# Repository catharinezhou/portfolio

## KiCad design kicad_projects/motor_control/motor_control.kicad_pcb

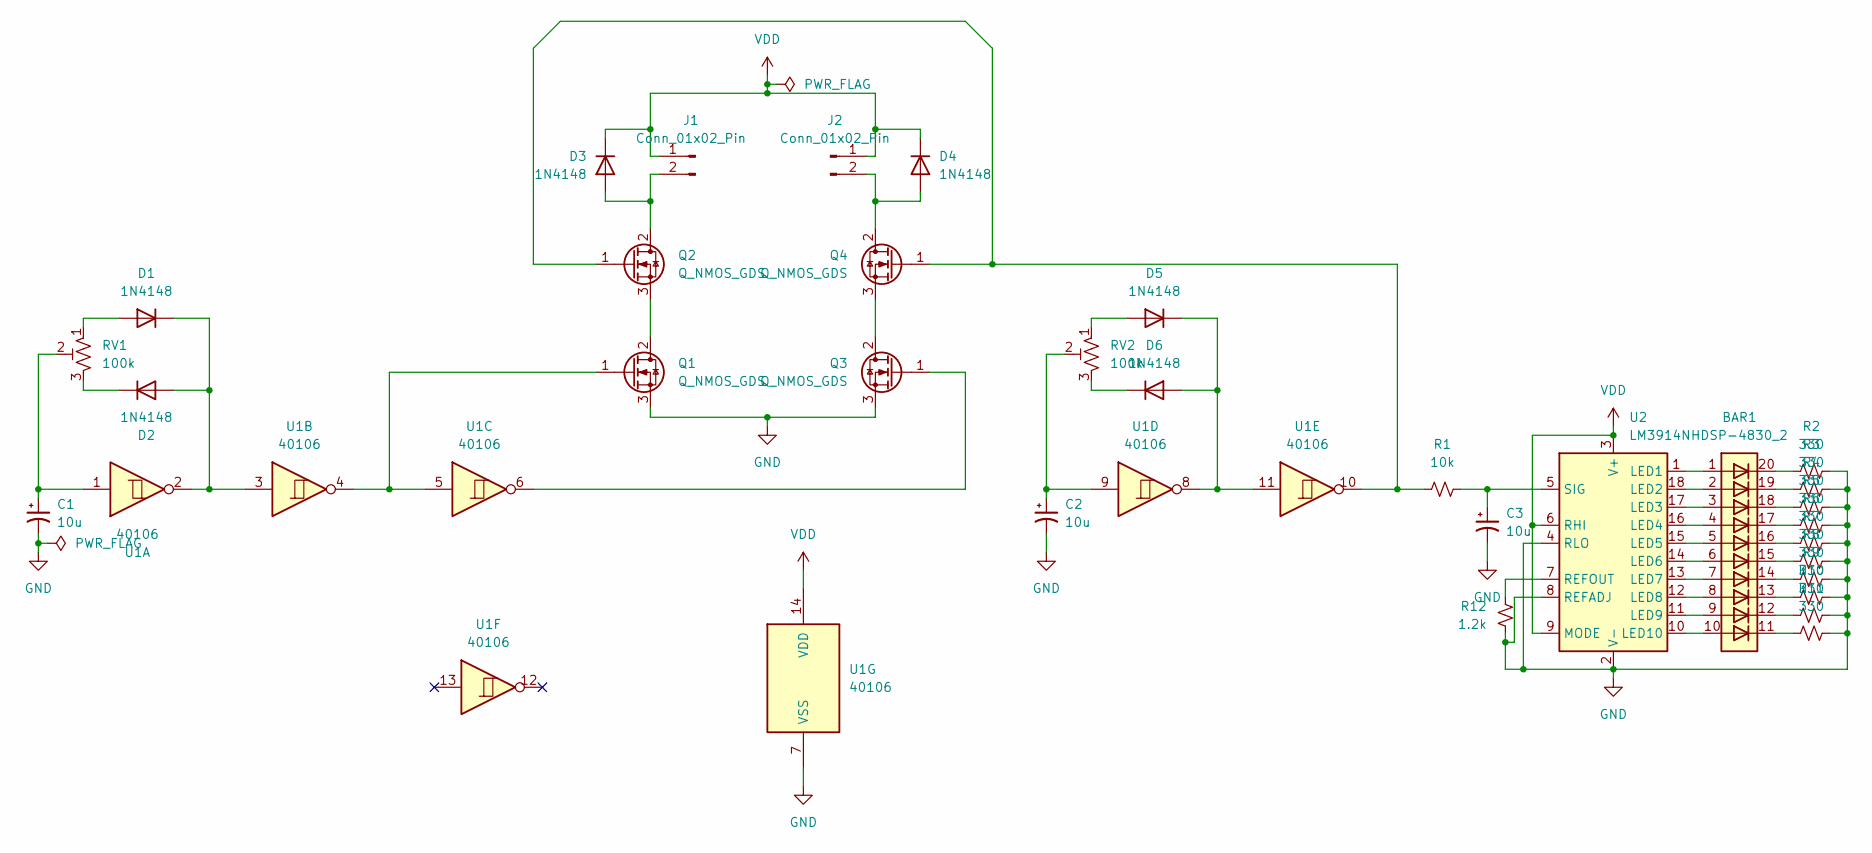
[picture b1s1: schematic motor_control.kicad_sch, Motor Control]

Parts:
BAR1: HDSP-4830_2; HDSP-4830
C1, C2, C3: 10u; CP_Radial_D6.3mm_P2.50mm
D1, D2, D3, D4, D5, D6: 1N4148; D_DO-35_SOD27_P7.62mm_Horizontal
J1, J2: Conn_01x02_Pin; TerminalBlock_Phoenix_MKDS-1,5-2-5.08_1x02_P5.08mm_Horizont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
Q1, Q2, Q3, Q4: Q_NMOS_GDS; TO-220-3_Vertical
R1: 10k; R_Axial_DIN0207_L6.3mm_D2.5mm_P10.16mm_Horizontal
R2, R3, R4, R5, R6, R7, R8, R9, R10, R11: 330; R_Axial_DIN0207_L6.3mm_D2.5mm_P10.16mm_Horizontal
R12: 1.2k; R_Axial_DIN0207_L6.3mm_D2.5mm_P10.16mm_Horizontal
RV1, RV2: 100k; Potentiometer_Bourns_3386P_Vertical
U1: 40106; DIP-14_W7.62mm
U2: LM3914N; DIP-18_W7.62mm

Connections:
GND: C1.2, C2.2, C3.2, Q1.3 (S), Q3.3 (S), R2.2, R3.2, R4.2, R5.2, R6.2, R7.2, R8.2, R9.2, R10.2, R11.2, R12.2, U1.7 (VSS), U2.2 (V-), U2.4 (RLO), U2.8 (REFADJ)
unnamed: BAR1.11 (K), R11.1
unnamed: BAR1.12 (K), R10.1
unnamed: BAR1.13 (K), R9.1
unnamed: BAR1.14 (K), R8.1
unnamed: BAR1.15 (K), R7.1
unnamed: BAR1.16 (K), R6.1
unnamed: BAR1.17 (K), R5.1
unnamed: BAR1.18 (K), R4.1
unnamed: BAR1.19 (K), R3.1
unnamed: BAR1.20 (K), R2.1
unnamed: C1.1, RV1.2, U1.1
unnamed: C2.1, RV2.2, U1.9
unnamed: D1.2 (A), RV1.1
unnamed: D1.1 (K), D2.2 (A), U1.2, U1.3
unnamed: D2.1 (K), RV1.3
unnamed: D3.2 (A), J1.2, Q2.2 (D)
unnamed: D4.2 (A), J2.2, Q4.2 (D)
unnamed: D5.2 (A), RV2.1
unnamed: D5.1 (K), D6.2 (A), U1.8, U1.11
unnamed: D6.1 (K), RV2.3
unnamed: Q1.2 (D), Q2.3 (S)
unnamed: Q1.1 (G), U1.4, U1.5
unnamed: Q2.1 (G), Q4.1 (G), R1.1, U1.10
unnamed: Q3.2 (D), Q4.3 (S)
unnamed: Q3.1 (G), U1.6
unnamed: BAR1.1 (A), U2.1 (LED1)
unnamed: BAR1.2 (A), U2.18 (LED2)
unnamed: BAR1.3 (A), U2.17 (LED3)
unnamed: BAR1.4 (A), U2.16 (LED4)
unnamed: BAR1.5 (A), U2.15 (LED5)
unnamed: BAR1.6 (A), U2.14 (LED6)
unnamed: BAR1.7 (A), U2.13 (LED7)
unnamed: BAR1.8 (A), U2.12 (LED8)
unnamed: BAR1.9 (A), U2.11 (LED9)
unnamed: BAR1.10 (A), U2.10 (LED10)
unnamed: R12.1, U2.7 (REFOUT)
unnamed: C3.1, R1.2, U2.5 (SIG)
VDD: D3.1 (K), D4.1 (K), J1.1, J2.1, U1.14 (VDD), U2.3 (V+), U2.6 (RHI), U2.9 (MODE)

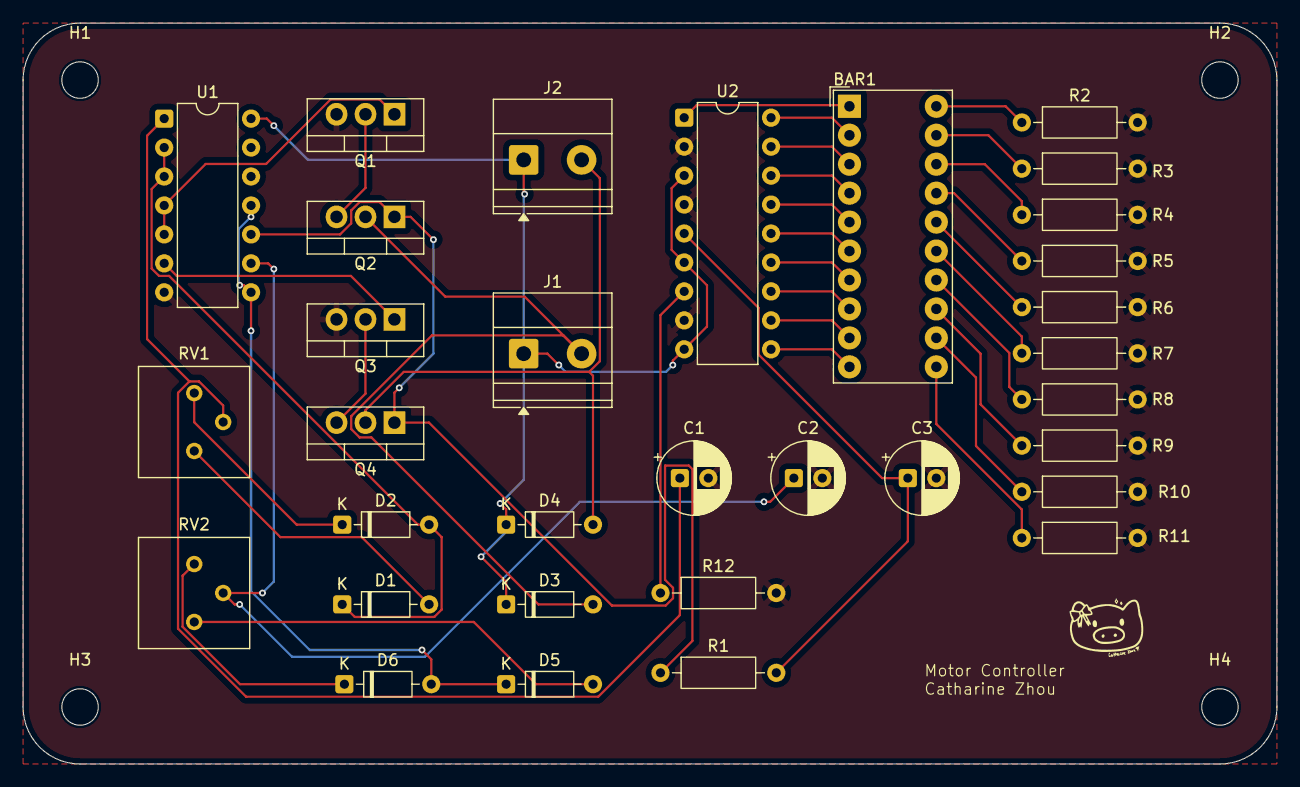
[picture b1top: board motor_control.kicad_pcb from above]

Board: 2 copper layers, 110.0 x 65.0 mm, 36 parts (0 on the bottom side), 39 nets.

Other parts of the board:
H1, H2, H3, H4: MountingHole; MountingHole_3.2mm_M3

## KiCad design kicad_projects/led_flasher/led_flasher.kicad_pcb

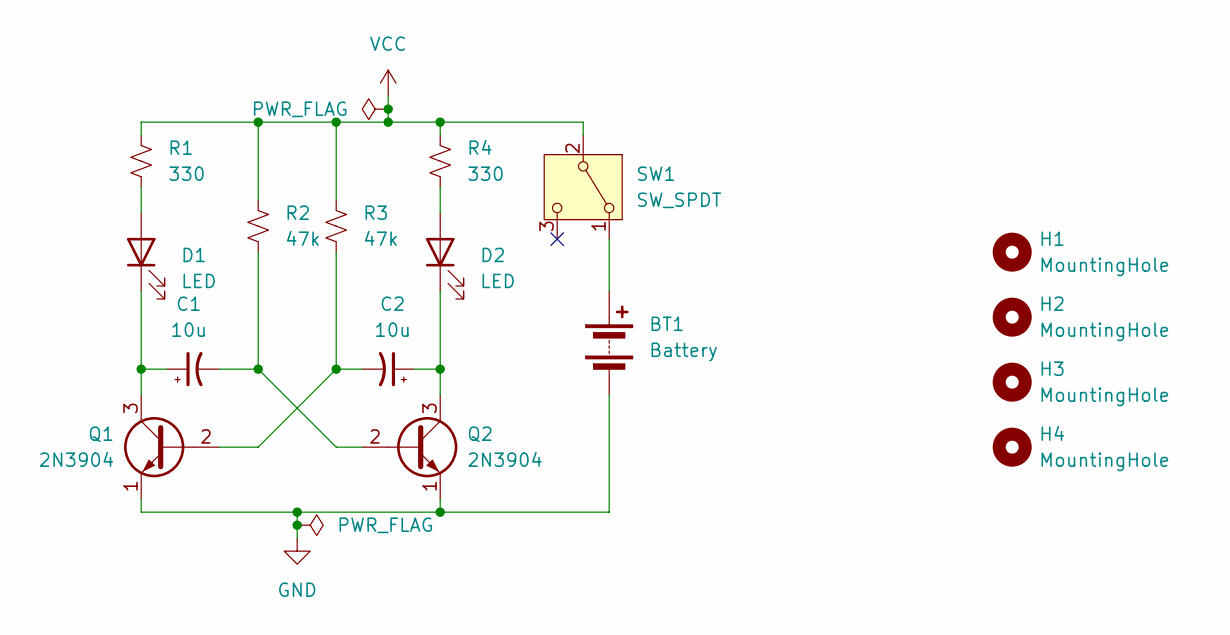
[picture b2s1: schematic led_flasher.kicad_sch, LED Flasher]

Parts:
BT1: Battery; BatteryHolder_Keystone_2479_3xAAA
C1, C2: 10u; CP_Radial_D6.3mm_P2.50mm
D1, D2: LED; LED_D5.0mm
H1, H2, H3, H4: MountingHole; MountingHole_3.2mm_M3
Q1, Q2: 2N3904; TO-92_Inline
R1, R4: 330; R_Axial_DIN0207_L6.3mm_D2.5mm_P10.16mm_Horizontal
R2, R3: 47k; R_Axial_DIN0207_L6.3mm_D2.5mm_P10.16mm_Horizontal
SW1: SW_SPDT; SW_E-Switch_EG1224_SPDT_Angled

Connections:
GND: BT1.2 (-), Q1.1 (E), Q2.1 (E)
unnamed: BT1.1 (+), SW1.1 (A)
unnamed: D1.2 (A), R1.2
unnamed: C1.1, D1.1 (K), Q1.3 (C)
unnamed: D2.2 (A), R4.2
unnamed: C2.1, D2.1 (K), Q2.3 (C)
unnamed: C2.2, Q1.2 (B), R3.2
unnamed: C1.2, Q2.2 (B), R2.2
VCC: R1.1, R2.1, R3.1, R4.1, SW1.2 (B)

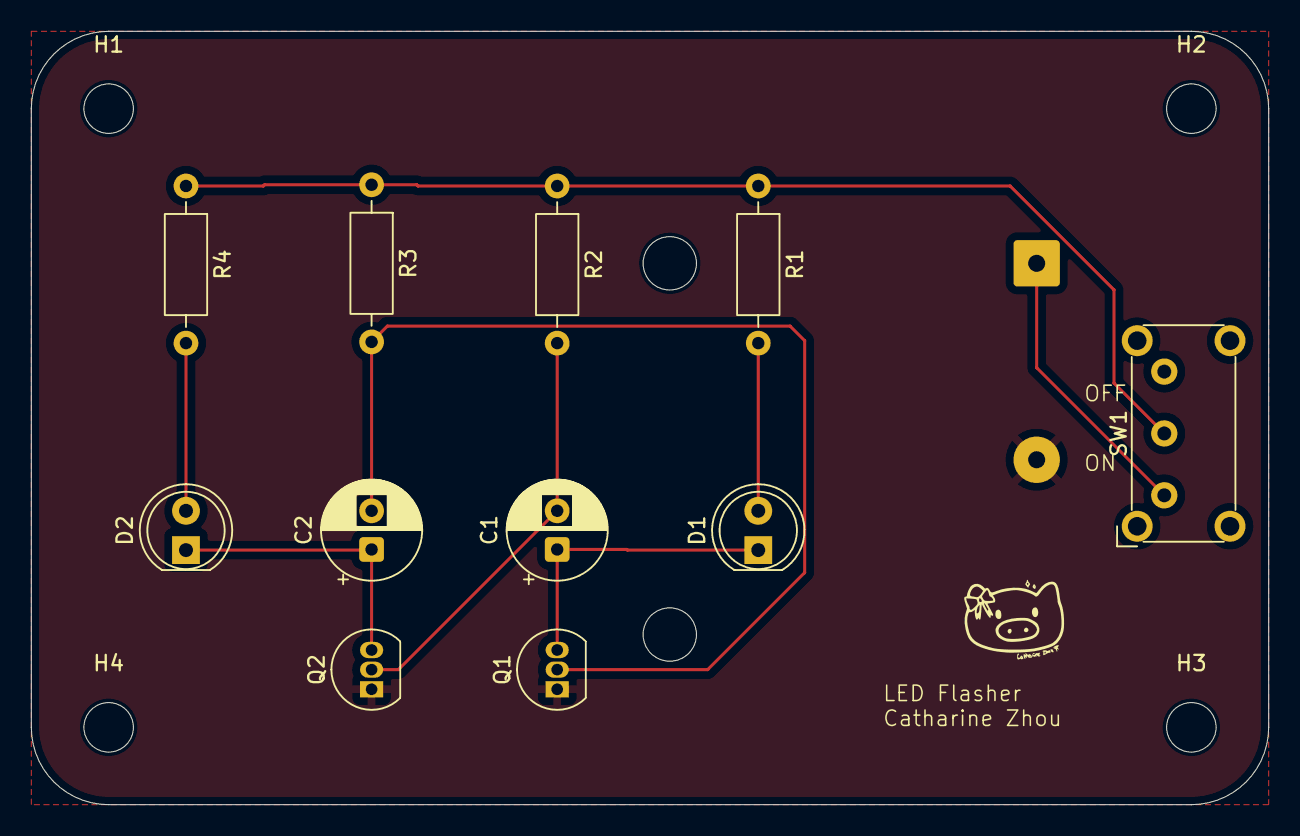
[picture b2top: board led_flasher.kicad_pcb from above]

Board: 2 copper layers, 80.0 x 50.0 mm, 16 parts (1 on the bottom side), 9 nets.
